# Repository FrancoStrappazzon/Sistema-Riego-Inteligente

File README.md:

# 💧 Sistema de Riego Inteligente con ESP32
Este proyecto implementa un sistema de riego automático basado en microcontrolador ESP32. Permite controlar una electroválvula en función de las condiciones de temperatura y humedad, e incluye visualización local mediante pantalla OLED y control remoto a través de la app Blynk.

## ⚙️ Características del sistema

  - Microcontrolador: ESP32-WROOM-32
  
  - Sensor: DHT11 (temperatura y humedad)

  - Actuador: Módulo relé 1CH controlando una electroválvula de 12V

  - Visualización local: Pantalla OLED 1.3” (I2C)

  - Visualización y control remoto: App Blynk IoT

  - Fuente: 3.3V (lógica), 12V (electroválvula)

## 🛠️ Herramientas utilizadas

- KiCad 9.0.0 – diseño de esquemático y PCB

- Blynk IoT – plataforma de control y visualización remota

- C++ / Arduino IDE – desarrollo del firmware

- Git + GitHub – control de versiones

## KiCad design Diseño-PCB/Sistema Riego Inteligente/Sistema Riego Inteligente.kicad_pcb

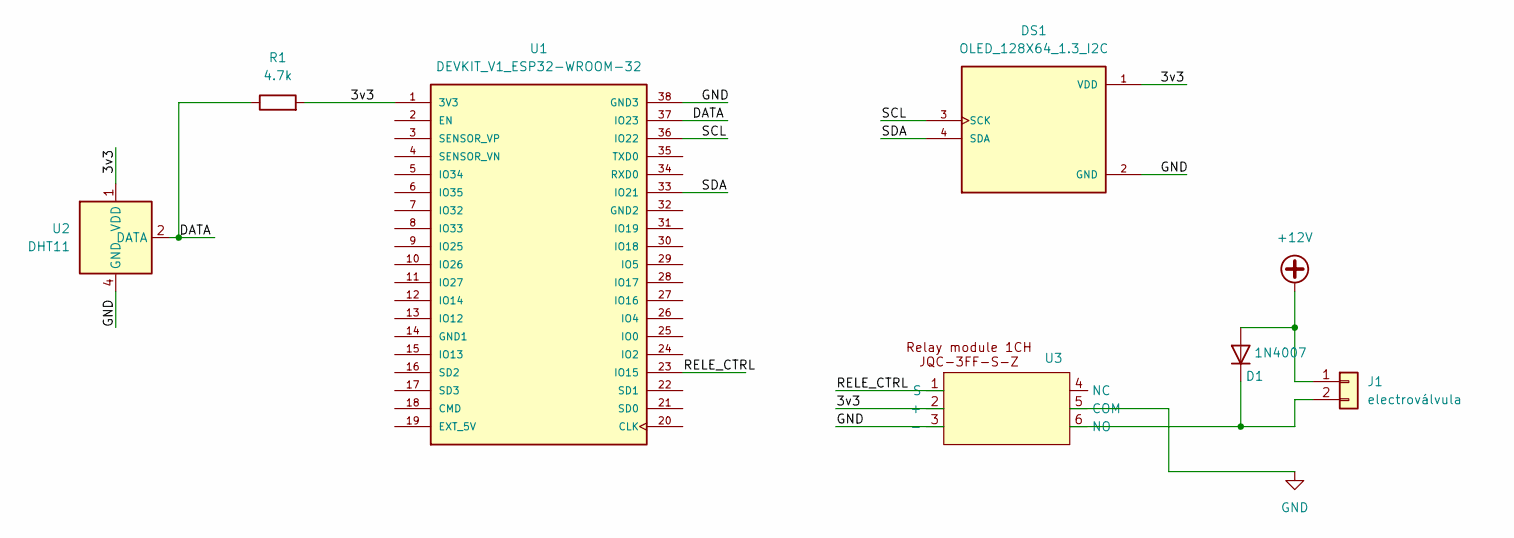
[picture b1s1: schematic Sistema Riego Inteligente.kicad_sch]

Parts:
D1: 1N4007; D_DO-41_SOD81_P10.16mm_Horizontal
DS1: OLED_128X64_1.3_I2C; LCD_OLED_128X64_1.3_I2C; PARTREV NA
J1: electroválvula; PhoenixContact_GMSTBA_2,5_2-G_1x02_P7.50mm_Horizontal
R1: 4.7k; R_1206_3216Metric
U1: DEVKIT_V1_ESP32-WROOM-32; MODULE_DEVKIT_V1_ESP32-WROOM-32; PARTREV N/A
U2: DHT11; Aosong_DHT11_5.5x12.0_P2.54mm
U3: Relay_Module_1CH

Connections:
+12V: D1.2 (A), J1.1
/3v3: DS1.1 (VDD), R1.2, U1.1 (3V3), U2.1 (VDD), U3.2 (+)
/DATA: R1.1, U1.37 (IO23), U2.2 (DATA)
/RELE_CTRL: U1.23 (IO15), U3.1 (S)
/SCL: DS1.3 (SCK), U1.36 (IO22)
/SDA: DS1.4 (SDA), U1.33 (IO21)
GND: DS1.2 (GND), U1.38 (GND3), U2.4 (GND), U3.3 (-), U3.5 (COM)
unnamed: D1.1 (K), J1.2, U3.6 (NO)

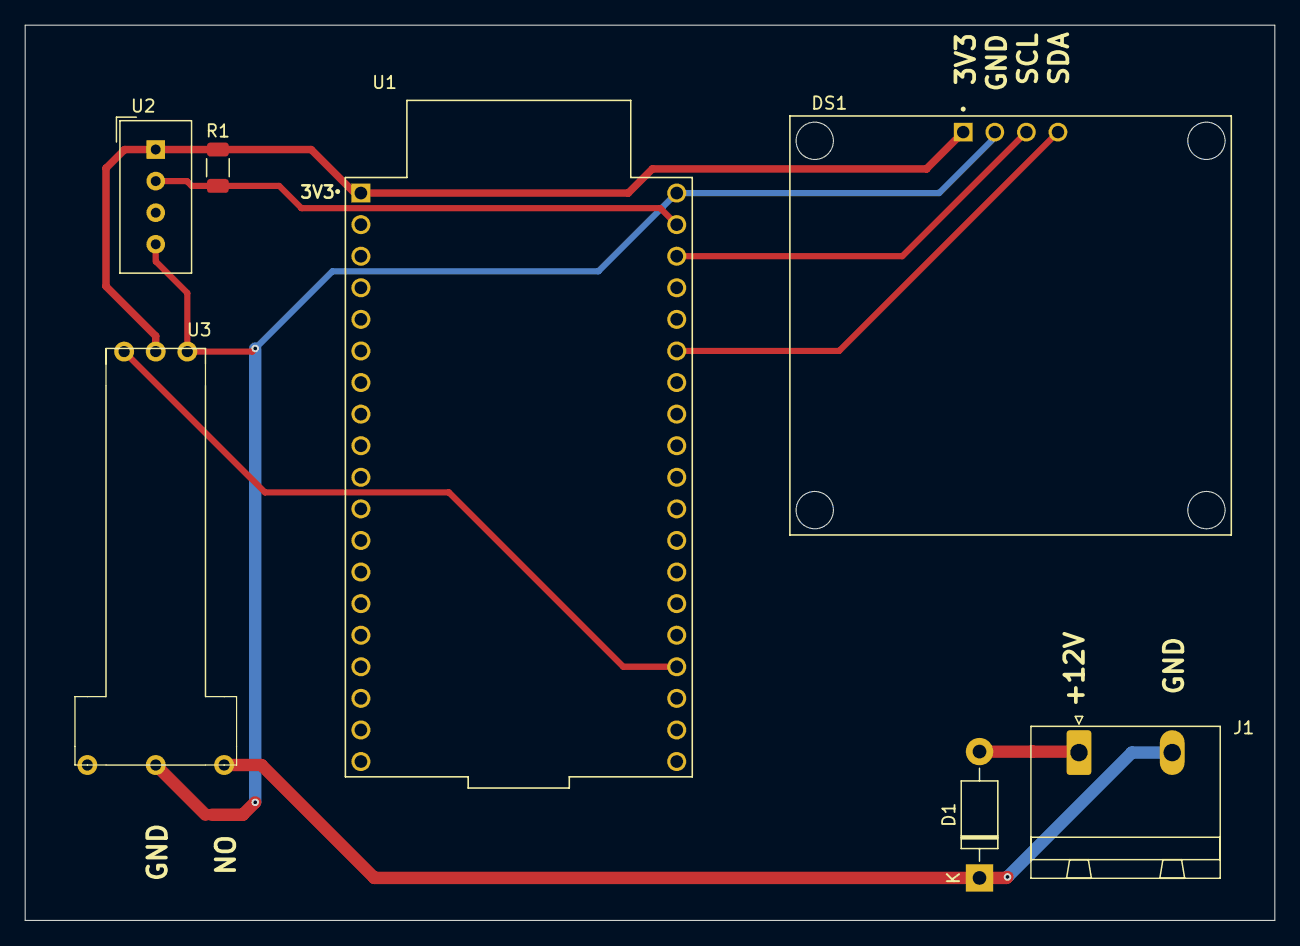
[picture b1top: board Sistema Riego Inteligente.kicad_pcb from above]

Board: 2 copper layers, 100.5 x 72.0 mm, 7 parts (0 on the bottom side), 8 nets.

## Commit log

2025-06-09 Primer commit, cargo código de ESP32
2025-06-10 Agrego conexion ESP32 con Blynk
2025-06-11 Agrego control desde app blynk en celular
2025-06-23 Actualizo footprints y PCB
2025-06-23 Actualizo esquemático
2025-06-24 Completo ruteo y diseño de PCB
